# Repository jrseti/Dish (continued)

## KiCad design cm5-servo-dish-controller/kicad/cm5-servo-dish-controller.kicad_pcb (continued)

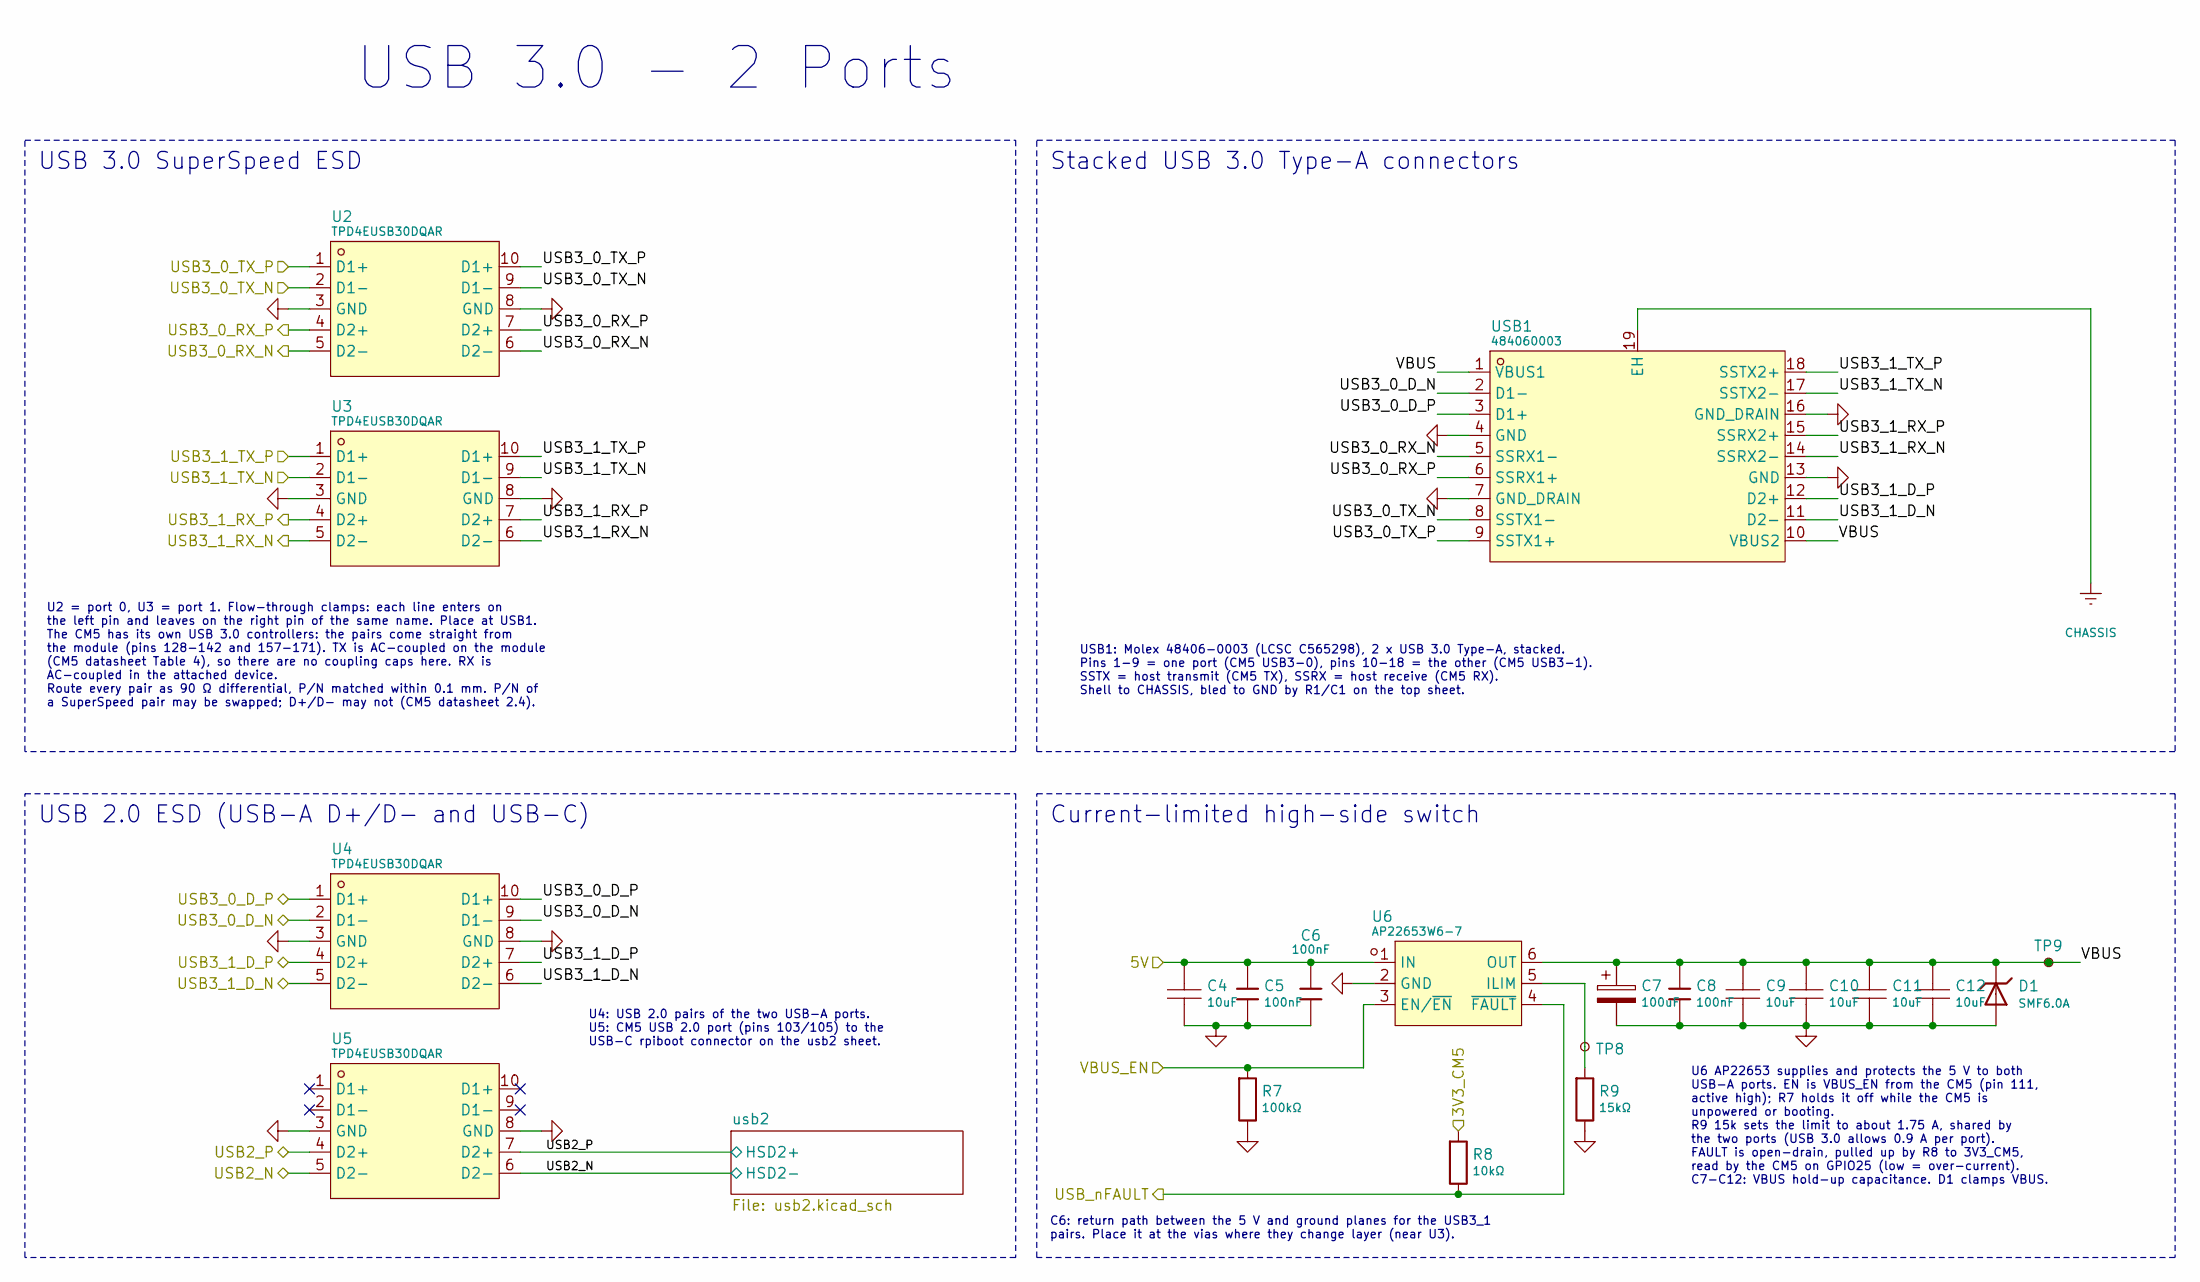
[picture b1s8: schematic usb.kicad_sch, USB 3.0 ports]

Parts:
C4, C9, C10, C11, C12: 10uF; CAPC2012X145N; Tolerance ±10%; Voltage Rating 10V; MPN CL21B106KPQNNNE; LCSC Part C32635
C5, C6, C8: 100nF; CAPC1005X55N; Tolerance ±10%; Voltage Rating 16V; MPN CL05B104KO5NNNC; LCSC Part C1525
C7: 100uF; CAPMP7343X310N; Tolerance ±20%; Voltage Rating 10V; MPN SA11AM101A19R15XXX; LCSC Part C135491
D1: SMF6.0A; SODFL3718X110N; MPN SMF6.0A; LCSC Part C19077499
R7: 100kΩ; RESC1608X55N; Tolerance ±1%; Voltage Rating 75V; MPN 0603WAF1003T5E; LCSC Part C25803
R8: 10kΩ; RESC1005X40N; Tolerance ±1%; Voltage Rating 50V; MPN 0402WGF1002TCE; LCSC Part C25744
R9: 15kΩ; RESC1005X40N; Tolerance ±1%; Voltage Rating 50V; MPN 0402WGF1502TCE; LCSC Part C25756
TP8, TP9: TestPoint_Small; TestPoint_Pad_D0.8mm
U2, U3, U4, U5: TPD4EUSB30DQAR; SON50P100X250X60-10N; MPN TPD4EUSB30DQAR; LCSC Part C90627
U6: AP22653W6-7; SOT95P280X145-6N; MPN AP22653W6-7; LCSC Part C2158037
USB1: 484060003; Molex_48406-0003; MPN 484060003; LCSC Part C565298

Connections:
/3V3_CM5: R8.1; also elsewhere on the board
/5V: C4.1, C5.1, C6.1, U6.1 (IN); also elsewhere on the board
/CM5/USB2_N: U5.5 (D2-), U5.6 (D2-); also elsewhere on the board
/CM5/USB2_P: U5.4 (D2+), U5.7 (D2+); also elsewhere on the board
/CM5/USB3_0_D_N: U4.2 (D1-), U4.9 (D1-), USB1.2 (D1-); also elsewhere on the board
/CM5/USB3_0_D_P: U4.1 (D1+), U4.10 (D1+), USB1.3 (D1+); also elsewhere on the board
/CM5/USB3_0_RX_N: U2.5 (D2-), U2.6 (D2-), USB1.5 (SSRX1-); also elsewhere on the board
/CM5/USB3_0_RX_P: U2.4 (D2+), U2.7 (D2+), USB1.6 (SSRX1+); also elsewhere on the board
/CM5/USB3_0_TX_N: U2.2 (D1-), U2.9 (D1-), USB1.8 (SSTX1-); also elsewhere on the board
/CM5/USB3_0_TX_P: U2.1 (D1+), U2.10 (D1+), USB1.9 (SSTX1+); also elsewhere on the board
/CM5/USB3_1_D_N: U4.5 (D2-), U4.6 (D2-), USB1.11 (D2-); also elsewhere on the board
/CM5/USB3_1_D_P: U4.4 (D2+), U4.7 (D2+), USB1.12 (D2+); also elsewhere on the board
/CM5/USB3_1_RX_N: U3.5 (D2-), U3.6 (D2-), USB1.14 (SSRX2-); also elsewhere on the board
/CM5/USB3_1_RX_P: U3.4 (D2+), U3.7 (D2+), USB1.15 (SSRX2+); also elsewhere on the board
/CM5/USB3_1_TX_N: U3.2 (D1-), U3.9 (D1-), USB1.17 (SSTX2-); also elsewhere on the board
/CM5/USB3_1_TX_P: U3.1 (D1+), U3.10 (D1+), USB1.18 (SSTX2+); also elsewhere on the board
/CM5/USB_nFAULT: R8.2, U6.4 (~FAULT); also elsewhere on the board
/CM5/VBUS_EN: R7.1, U6.3 (EN/~EN); also elsewhere on the board
/CM5/usb/VBUS: C7.1, C8.1, C9.1, C10.1, C11.1, C12.1, D1.1, TP9.1 (1_1), U6.6 (OUT), USB1.1 (VBUS1), USB1.10 (VBUS2)
CHASSIS: USB1.19 (EH); also elsewhere on the board
GND: C4.2, C5.2, C6.2, C7.2, C8.2, C9.2, C10.2, C11.2, C12.2, D1.2, R7.2, R9.2, U2.3 (GND), U2.8 (GND), U3.3 (GND), U3.8 (GND), U4.3 (GND), U4.8 (GND), U5.3 (GND), U5.8 (GND), U6.2 (GND), USB1.4 (GND), USB1.7 (GND_DRAIN), USB1.13 (GND), USB1.16 (GND_DRAIN); also elsewhere on the board
unnamed: R9.1, TP8.1 (1_1), U6.5 (ILIM)

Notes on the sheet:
USB 3.0 - 2 Ports
U2 = port 0, U3 = port 1. Flow-through clamps: each line enters on the left pin and leaves on the right pin of the same name. Place at USB1. The CM5 has its own USB 3.0 controllers: the pairs come straight from the module (pins 128-142 and 157-171). TX is AC-coupled on the module (CM5 datasheet Tab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
USB 2.0 ESD (USB-A D+/D- and USB-C)
Stacked USB 3.0 Type-A connectors
U6 AP22653 supplies and protects the 5 V to both USB-A ports. EN is VBUS_EN from the CM5 (pin 111, active high); R7 holds it off while the CM5 is unpowered or booting. R9 15k sets the limit to about 1.75 A, shared by the two ports (USB 3.0 allows 0.9 A per port). FAULT is open-drain, pulled up by R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
C6: return path between the 5 V and ground planes for the USB3_1 pairs. Place it at the vias where they change layer (near U3).
USB 3.0 SuperSpeed ESD
USB1: Molex 48406-0003 (LCSC C565298), 2 x USB 3.0 Type-A, stacked. Pins 1-9 = one port (CM5 USB3-0), pins 10-18 = the other (CM5 USB3-1). SSTX = host transmit (CM5 TX), SSRX = host receive (CM5 RX). Shell to CHASSIS, bled to GND by R1/C1 on the top sheet.
U4: USB 2.0 pairs of the two USB-A ports. U5: CM5 USB 2.0 port (pins 103/105) to the USB-C rpiboot connector on the usb2 sheet.
Current-limited high-side switch

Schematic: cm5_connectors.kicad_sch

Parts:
C14: 100nF; CAPC1005X55N; Tolerance ±10%; Voltage Rating 16V; MPN CL05B104KO5NNNC; LCSC Part C1525
F1: 100mA; FUSC1608X100N; MPN SMD0603-010-24V; LCSC Part C70048
H6: Header-Male-2.54_1x2; PinHeader_1x02_P2.54mm_Vertical; MPN B-2100S02P-A110; LCSC Part C124375
J3: 2541WV-2X12P; PinHeader_2x12_P2.54mm_Vertical; MPN 2541WV-2x12P; LCSC Part C5383110
J4: Header-Male-2.54_1x3; PinHeader_1x03_P2.54mm_Vertical; MPN 2.54-1*3PPin; LCSC Part C49257
J5: Header-Male-2.54_2x3; PinHeader_2x03_P2.54mm_Vertical; MPN 2.54-2*3PPin; LCSC Part C65114
R12, R13: 2.2kΩ; RESC1005X40N; Tolerance ±1%; Voltage Rating 50V; MPN 0402WGF2201TCE; LCSC Part C25879
U9: 74LVC1G07SE-7; SOT65P210X110-5N; MPN 74LVC1G07SE-7; LCSC Part C67531

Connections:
/3V3_CM5: C14.1, F1.1, H6.1, U9.5 (VCC); also elsewhere on the board
/5V: J3.7; also elsewhere on the board
/CM5/BOOT_CONSOLE_RXD: J4.1; also elsewhere on the board
/CM5/BOOT_CONSOLE_TXD: J4.2; also elsewhere on the board
/CM5/CM5_Connectors/I2C1_PU: H6.2, R12.1, R13.1
/CM5/EEPROM_nWP: J5.4; also elsewhere on the board
/CM5/GPIO0: J3.13; also elsewhere on the board
/CM5/GPIO17: J3.20; also elsewhere on the board
/CM5/GPIO19: J3.11; also elsewhere on the board
/CM5/GPIO22: J3.21; also elsewhere on the board
/CM5/GPIO26: J3.9; also elsewhere on the board
/CM5/GPIO27: J3.23; also elsewhere on the board
/CM5/I2C1_SCL: J3.22, R13.2; also elsewhere on the board
/CM5/I2C1_SDA: J3.24, R12.2; also elsewhere on the board
/CM5/PMIC_EN: J5.6; also elsewhere on the board
/CM5/SPI0_CE0: J3.14; also elsewhere on the board
/CM5/SPI0_CE1: J3.12; also elsewhere on the board
/CM5/SPI0_MISO: J3.17; also elsewhere on the board
/CM5/SPI0_MOSI: J3.19; also elsewhere on the board
/CM5/SPI0_SCLK: J3.15; also elsewhere on the board
/CM5/nPWR_CYCLE: U9.2 (A); also elsewhere on the board
/CM5/nRPIBOOT: J5.2; also elsewhere on the board
GND: C14.2, J3.1, J3.2, J3.3, J3.4, J3.6, J3.8, J3.10, J3.16, J3.18, J4.3, J5.1, J5.3, U9.3 (GND); also elsewhere on the board
unnamed: F1.2, J3.5
unnamed: J5.5, U9.4 (Y)

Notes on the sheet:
Boot Console UART
I2C Pull-Ups
GPIO2
GPIO0 (J3-13) as plain GPIO: add to config.txt force_eeprom_read=0 disable_poe_fan=1 or the firmware probes GPIO0/1 (I2C0) for a HAT EEPROM at boot.
EEPROM WRITE PROTECT (EEPROM_nWP, J5 3-4) The CM5 pulls EEPROM_nWP up internally (100k), so the bootloader EEPROM is writable unless J5 3-4 is fitted. The jumper only takes effect once protection is enabled in the bootloader config (CM5 datasheet 2.12.2). Production: - Set eeprom_write_protect=1 in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
H6: optional I2C1 pull-ups R12/R13, normally OPEN. CM5 already pulls GPIO2/3 up with 1.8k (CM5 datasheet Table 4). Fit H6 only for a long, high-capacitance bus at 400 kHz: ~1k total, ~2.9 mA sink at 0.4 V (I2C spec min 3 mA, so compliant devices are OK).
I2C PULL-UPS I2C1: GPIO2 = I2C1_SDA (J3-24), GPIO3 = I2C1_SCL (J3-22) Pulled up to 3.3 V (GPIO_VREF) by 1.8 kΩ inside the CM5 (CM5 datasheet Table 4, pins 56/58). No board pull-ups are needed. R12/R13 (2.2k, fitted via H6) are optional.
EEPROM write protect = Jumper Pins 3-4
GPIO3
CONSOLE UART (J4): CM5 UART0, 3.3 V logic, 115200 baud, 8N1, no flow control J4-1 BOOT_CONSOLE_RXD (GPIO15, CM5 receives) <- adapter TXD J4-2 BOOT_CONSOLE_TXD (GPIO14, CM5 transmits) -> adapter RXD J4-3 GND -- adapter GND TX and RX cross over: the adapter TXD goes to the CM5 RXD. Use an inexpensive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
J3 pins 2 and 4 are GND. On the CM4 board they were the AIN0/AIN1 ADC inputs. The CM5 has no ADC pins (module pins 94/96 are now CC1/CC2), so the inputs and their clamps are removed.
CM5 External Header Pins
GPIO9
GPIO10
Boot/EEPROM_EN/PMIC_EN
POWER-CYCLE CONTROL (nPWR_CYCLE) Lets the CM5 cut its own power after a clean shutdown and restart by itself. Use it when a normal reboot is not enough: it fully resets the PMIC and all on-module power rails. How it works: - GPIO6 drives U9 (74LVC1G07, open-drain). J5 pins 5-6 connect U9's output t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
GPIO8
GPIO7
Force RPIBOOT = Jumper Pins 1-2
F1 (100 mA PTC, SMD0603-010-24V) fuses the 3.3 V on J3 pin 5: a short on a plug-in board trips F1, not the CM5 rail. HAT budget 100 mA; CN1 has F3.
GPIO Headers
GPIO11

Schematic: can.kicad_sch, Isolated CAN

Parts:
C46, C47, C50, C51, C52, C62: 100nF; CAPC1005X55N; Tolerance ±10%; Voltage Rating 16V; MPN CL05B104KO5NNNC; LCSC Part C1525
C48, C53: 1uF; CAPC1608X95N; Tolerance ±10%; Voltage Rating 50V; MPN CL10A105KB8NNNC; LCSC Part C15849
C49, C57, C60: 2.2uF; CAPC3216X180N; MPN CL31Y225KCHVPNE; LCSC Part C2803390
C54: 2.2nF; CAPRD1000W55L820T450; Tolerance ±20%; Voltage Rating 400VAC Y1; MPN AJTF222M2GF0200A082E; LCSC Part C2836435; not fitted
C55: 220nF; CAPC1005X55N; Tolerance ±10%; Voltage Rating 25V; MPN TCC0402X7R224K250AT; LCSC Part C915854
C56: 100uF; CAPAE1030X1250N; MPN EFVH100ADA101M10C0; LCSC Part C22387799
C58, C64: 4.7nF; CAPC3216X180N; Tolerance ±10%; Voltage Rating 2kV; MPN 1206B472K202NT; LCSC Part C41017; not fitted
C59: 4.7nF; CAPC2012X145N; Tolerance ±5%; Voltage Rating 50V; MPN GRM2165C1H472JA01D; LCSC Part C77063
C61: 100nF; CAPC1608X95N; Tolerance ±10%; Voltage Rating 100V; MPN CL10B104KC8NNNC; LCSC Part C15725
C63: 22uF; CAPC2012X145N; Tolerance ±20%; Voltage Rating 25V; MPN CL21A226MAYNNNE; LCSC Part C602037
D8: SMBJ28CA; DIOM5436X244N; MPN SMBJ28CA; LCSC Part C151259
D9, D11: PESD2CANFD27V; SOT95P240X110-3N; MPN PESD2CANFD27V-TR-(TP); LCSC Part C54561881
D10: SS210; DIOM5226X244N; MPN SS210; LCSC Part C14996
D12: SMBJ28A; DIOM5436X244N; MPN SMBJ28A; LCSC Part C178227
J11: KF2EDGR-5.08-2P; KEFA_KF2EDGR-5.08-2P; MPN KF2EDGR-5.08-2P; LCSC Part C441204
J12, J13: RJ45; Kinghelm_KH-RJ45-58-8P8C; MPN KH-RJ45-58-8P8C; LCSC Part C2683360
L2: 51uH; TDK_ACT45B; MPN ACT45B-510-2P-TL003; LCSC Part C76584
L3: 33uH; INDM6060X450N; Tolerance ±20%; Current Rating 1.5A; MPN SMNR6045-330MT; LCSC Part C135306
LED7: GREEN; LEDC2012X110N; MPN KT-0805G; LCSC Part C2297
R38: 33Ω; RESC1005X40N; Tolerance ±1%; Voltage Rating 50V; MPN 0402WGF330JTCE; LCSC Part C25105
R39, R42, R47: 10kΩ; RESC1005X40N; Tolerance ±1%; Voltage Rating 50V; MPN 0402WGF1002TCE; LCSC Part C25744
R40: 249kΩ; RESC1608X55N; Tolerance ±1%; Voltage Rating 75V; MPN 0603WAF2493T5E; LCSC Part C22918
R41: 30kΩ; RESC1005X40N; Tolerance ±1%; Voltage Rating 50V; MPN 0402WGF3002TCE; LCSC Part C25776
R43: 24kΩ; RESC1005X40N; Tolerance ±1%; Voltage Rating 50V; MPN 0402WGF2402TCE; LCSC Part C25769
R44, R45: 0Ω; RESC1608X55N; Tolerance ±1%; Voltage Rating 75V; MPN 0603WAF0000T5E; LCSC Part C21189; not fitted
R46: 20kΩ; RESC1005X40N; Tolerance ±1%; Voltage Rating 50V; MPN 0402WGF2002TCE; LCSC Part C25765
R48, R50: 47kΩ; RESC1005X40N; Tolerance ±1%; Voltage Rating 50V; MPN 0402WGF4702TCE; LCSC Part C25792
R49, R60: 0Ω; RESC3216X70N; Tolerance ±1%; Voltage Rating 200V; MPN 1206W4F0000T5E; LCSC Part C17888
R51, R59: 1MΩ; RESC3216X70N; Tolerance ±1%; Voltage Rating 200V; MPN 1206W4F1004T5E; LCSC Part C17927; not fitted
R52: 0Ω; RESC1608X55N; Tolerance ±1%; Voltage Rating 75V; MPN 0603WAF0000T5E; LCSC Part C21189
R53: 10kΩ; RESC1608X55N; Tolerance ±1%; Voltage Rating 75V; MPN 0603WAF1002T5E; LCSC Part C25804
R54, R55: 60.4Ω; RESC3216X70N; Tolerance ±1%; Voltage Rating 200V; MPN 1206W4F604JT5E; LCSC Part C57572
R56: 100kΩ; RESC1608X55N; Tolerance ±1%; Voltage Rating 75V; MPN 0603WAF1003T5E; LCSC Part C25803
R57: 118kΩ; RESC1005X40N; Tolerance ±1%; Voltage Rating 50V; MPN 0402WGF1183TCE; LCSC Part C25748
R58: 22.1kΩ; RESC1005X40N; Tolerance ±1%; Voltage Rating 50V; MPN FRC0402F2212TS; LCSC Part C2929993
SW2: 2xSPST; SOP127P835X250-4N; MPN DSHP02TSGER; LCSC Part C3293142
TP31, TP32, TP33, TP34, TP35, TP36, TP37, TP38, TP39, TP40, TP41: TestPoint_Small; TestPoint_Pad_D0.8mm
U17: ISO1042DWR; SOIC127P1030X265-16N; MPN ISO1042DWR; LCSC Part C1848126
U18: ISO7721DWR; SOIC127P1030X265-16N; MPN ISO7721DWR; LCSC Part C524805
U19: TPS26600PWPR; SOP65P640X120-17N; MPN TPS26600PWPR; LCSC Part C544399
U20: LMR51606XDBVR; SOT95P280X145-6N; MPN LMR51606XDBVR; LCSC Part C21260865

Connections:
/STM32/3V3_MCU: C46.1, C47.1, C48.1, R39.1, U17.1 (VCC1), U18.3 (VCC1); also elsewhere on the board
/STM32/CAN/5V_ISO: C50.1, C51.1, C52.1, C53.1, C63.1, L3.2, R48.1, R57.1, TP41.1 (1_1), U17.11 (VCC2), U17.16 (VCC2), U18.14 (VCC2)
/STM32/CAN/24V_ISO_IN: C49.1, D8.2, D10.2 (A), J11.1, R40.1, U19.1 (IN), U19.2 (IN)
/STM32/CAN/BUCK_FB: R57.2, R58.1, TP40.1 (1_1), U20.3 (FB)
/STM32/CAN/CANH_T: L2.1, R44.1, U17.13 (CANH)
/STM32/CAN/CANL_T: L2.2, R45.1, U17.12 (CANL)
/STM32/CAN/CAN_H: D9.2, D11.2, J12.1, J13.1, L2.4, R44.2, SW2.4, TP36.1 (1_1)
/STM32/CAN/CAN_L: D9.1, D11.1, J12.2, J13.2, L2.3, R45.2, SW2.3, TP37.1 (1_1)
/STM32/CAN/CAN_V+: C56.1, C57.1, D12.1 (C), J13.8, R53.1, TP35.1 (1_1), U19.15 (OUT), U19.16 (OUT)
/STM32/CAN/EFUSE_RTN: C55.2, R42.2, R43.2, U19.6 (MODE), U19.8 (RTN), U19.17 (EP)
/STM32/CAN/EN_ISO: R47.2, U18.12 (OUTB)
/STM32/CAN/FLT_ISO: R50.2, U18.13 (INA)
/STM32/CAN/SHLD_A: C58.1, J12.9, J12.10, R49.1, R51.1
/STM32/CAN/SHLD_B: C64.1, J13.9, J13.10, R59.1, R60.1
/STM32/CAN/VIN_BUCK: C60.1, C61.1, D10.1 (K), R56.1, TP38.1 (1_1), U20.5 (VIN)
/STM32/CAN_RX: U17.5 (RXD); also elsewhere on the board
/STM32/CAN_TX: R38.1; also elsewhere on the board
/STM32/CAN_VBUS_EN: U18.5 (INB); also elsewhere on the board
/STM32/CAN_VBUS_FLT: U18.4 (OUTA); also elsewhere on the board
CHASSIS: C58.2, C64.2, R49.2, R51.2, R59.2, R60.2; also elsewhere on the board
GND: C46.2, C47.2, C48.2, C54.1, U17.2 (GND1), U17.8 (GND1), U18.1 (GND1), U18.7 (GND1); also elsewhere on the board
GND_ISO: C49.2, C50.2, C51.2, C52.2, C53.2, C54.2, C56.2, C57.2, C59.2, C60.2, C61.2, C63.2, D8.1, D9.3, D11.3, D12.2 (A), J11.2, J13.3, J13.7, LED7.2 (K), R46.2, R52.2, R58.2, TP31.1 (1_1), U17.9 (GND2), U17.10 (GND2), U17.15 (GND2), U18.9 (GND2), U18.16 (GND2), U19.9 (GND), U20.2 (GND)
unnamed: C59.1, R54.2, R55.2
unnamed: J12.3, R52.1
unnamed: LED7.1 (A), R53.2, TP34.1 (1_1)
unnamed: R54.1, SW2.1
unnamed: R55.1, SW2.2
unnamed: R38.2, R39.2, U17.3 (TXD)
unnamed: R43.1, TP33.1 (1_1), U19.11 (ILIM)
unnamed: R41.2, R42.1, U19.5 (OVP)
unnamed: R40.2, R41.1, TP32.1 (1_1), U19.3 (UVLO)
unnamed: C55.1, U19.12 (dVdT)
unnamed: R48.2, R50.1, U19.14 (~FLT)
unnamed: R46.1, R47.1, U19.7 (~SHDN)
unnamed: C62.1, U20.1 (CB)
unnamed: R56.2, TP39.1 (1_1), U20.4 (EN)
unnamed: C62.2, L3.1, U20.6 (SW)

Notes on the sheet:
Digital isolator for the eFuse enable and fault signals
Isolated CAN transceiver and common-mode choke
Isolated CAN section, 2-jack single-bus version (design brief plans/isolated-can-section-brief.md, rev C1). This board is the CANopen master in the middle of one linear bus: [120 ohm] drive EL -- drive AZ -- J12 == this board == J13 -- weather bridge -- AZ node -- EL node [120 ohm] Three domains, k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
Isolated CAN (CANopen)
J12 CAN A - drives (no power)
GND_ISO
5V_ISO supply for the isolated side
U18 ISO7721 (DW, SOIC-16 wide, 8 mm creepage) crosses the same isolation barrier as U17. CAN_VBUS_EN (PC8): high or not driven = dish-side CAN_V+ on, low = off. The ISO7721 output defaults high when its input is open or the logic side is unpowered, so CAN_V+ comes up without firmware. CAN_VBUS_FLT 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
+24 V GND_ISO
CAN bus through-path, protection, termination and RJ45 jacks
J12 = CAN A, drive side (to DSY-C CN1). J13 = CAN B, dish side (weather bridge, AZ node, EL node). Silkscreen J13 "CAN + 24 V OUT - DISH": it carries power that must never reach a drive. Both jacks use the CiA 303-1 pinout: pin 1 CAN_H, pin 2 CAN_L. CAN_H / CAN_L run straight from J12 to J13 as one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
stub to L2 / U17
SW2 default OFF
J13 CAN B - dish (CAN_V+ out)
J11: 24 V from the external isolated Mean Well 48 V to 24 V converter. Its -V output stays floating: no bond to PE or to board GND. D8 SMBJ28CA (28 V stand-off, 45 V clamp) is bidirectional, so a reversed supply is blocked by U19 and not shorted by the TVS. U19 TPS26600 eFuse: current limit 12 / R4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
U17 ISO1042 (DW, SOIC-16 wide): isolated CAN FD transceiver, 5 Mbit/s, 5 kVrms, +/-70 V bus fault protection. Logic side on 3V3_MCU / GND: C46 100 nF + C48 1 uF at VCC1. Bus side on 5V_ISO / GND_ISO: this package has two VCC2 pins, each with its own 100 nF (C50 at pin 16, C52 at pin 11), plus C53 1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
24 V isolated input and CAN_V+ eFuse (dish-side bus power)
U20 LMR51606X: 65 V, 0.6 A synchronous buck, 400 kHz. Output 0.8 V x (1 + R57 / R58) = 5.07 V. Load: U17 up to about 75 mA while it drives the bus dominant, U18 about 2 mA. D10 feeds it from the input side of the eFuse: U17 keeps talking to the drives while CAN_V+ is switched off. D10 also blocks a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

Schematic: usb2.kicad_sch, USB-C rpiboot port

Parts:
D7: SMF6.0A; SODFL3718X110N; MPN SMF6.0A; LCSC Part C19077499
R36, R37: 5.1kΩ; RESC1005X40N; Tolerance ±1%; Voltage Rating 50V; MPN 0402WGF5101TCE; LCSC Part C25905
TP30: TestPoint_Small; TestPoint_Pad_D0.8mm
USBC1: TYPE-C-31-M-12; HRO_TYPE-C-31-M-12; MPN TYPE-C-31-M-12; LCSC Part C165948

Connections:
/CM5/USB2_N: USBC1.A7 (DN1), USBC1.B7 (DN2); also elsewhere on the board
/CM5/USB2_P: USBC1.A6 (DP1), USBC1.B6 (DP2); also elsewhere on the board
/CM5/usb/usb2/VBUS_USBC: D7.1, TP30.1 (1_1), USBC1.A4B9 (VBUS), USBC1.B4A9 (VBUS)
CHASSIS: USBC1.1 (EH), USBC1.2 (EH), USBC1.3 (EH), USBC1.4 (EH); also elsewhere on the board
GND: D7.2, R36.2, R37.2, USBC1.A1B12 (GND), USBC1.B1A12 (GND); also elsewhere on the board
unnamed: R36.1, USBC1.A5 (CC1)
unnamed: R37.1, USBC1.B5 (CC2)

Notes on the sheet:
USB-C Port for CM5 Flashing (rpiboot)
USB-C carries the CM5 USB 2.0 port (module pins 103/105). It is a device port for rpiboot (eMMC flashing) only. There is no mux: on the CM5 the two USB-A ports have their own USB 3.0 controllers. USB_OTG_ID (module pin 101) is left open = device role. USBC1 VBUS is not used (the board takes no powe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

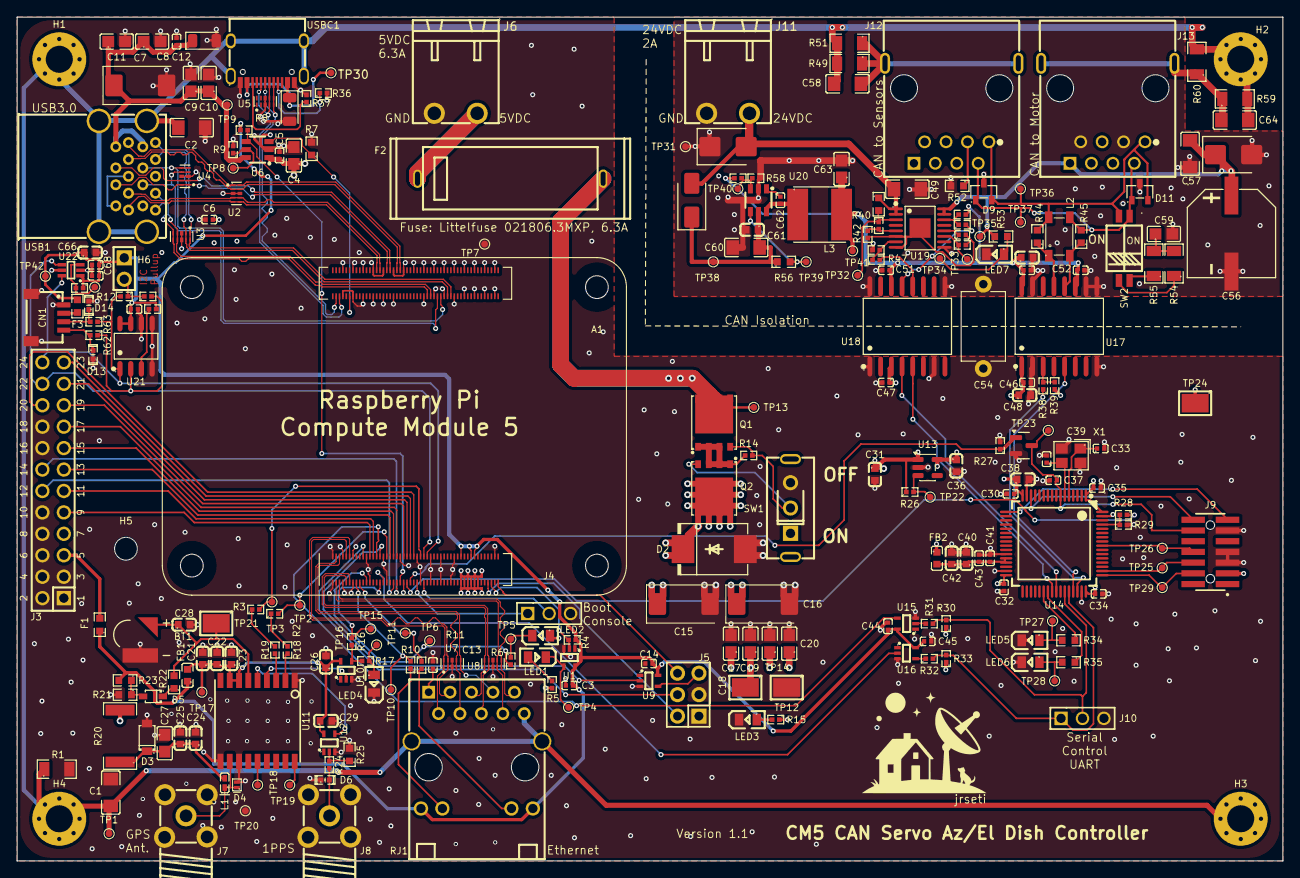
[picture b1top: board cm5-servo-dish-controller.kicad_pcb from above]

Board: 4 copper layers, 150.0 x 100.0 mm, 259 parts (1 on the bottom side), 154 nets.

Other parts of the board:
LOGO1: LOGO; house-dog-logo
LOGO2: dog-ufo-logo

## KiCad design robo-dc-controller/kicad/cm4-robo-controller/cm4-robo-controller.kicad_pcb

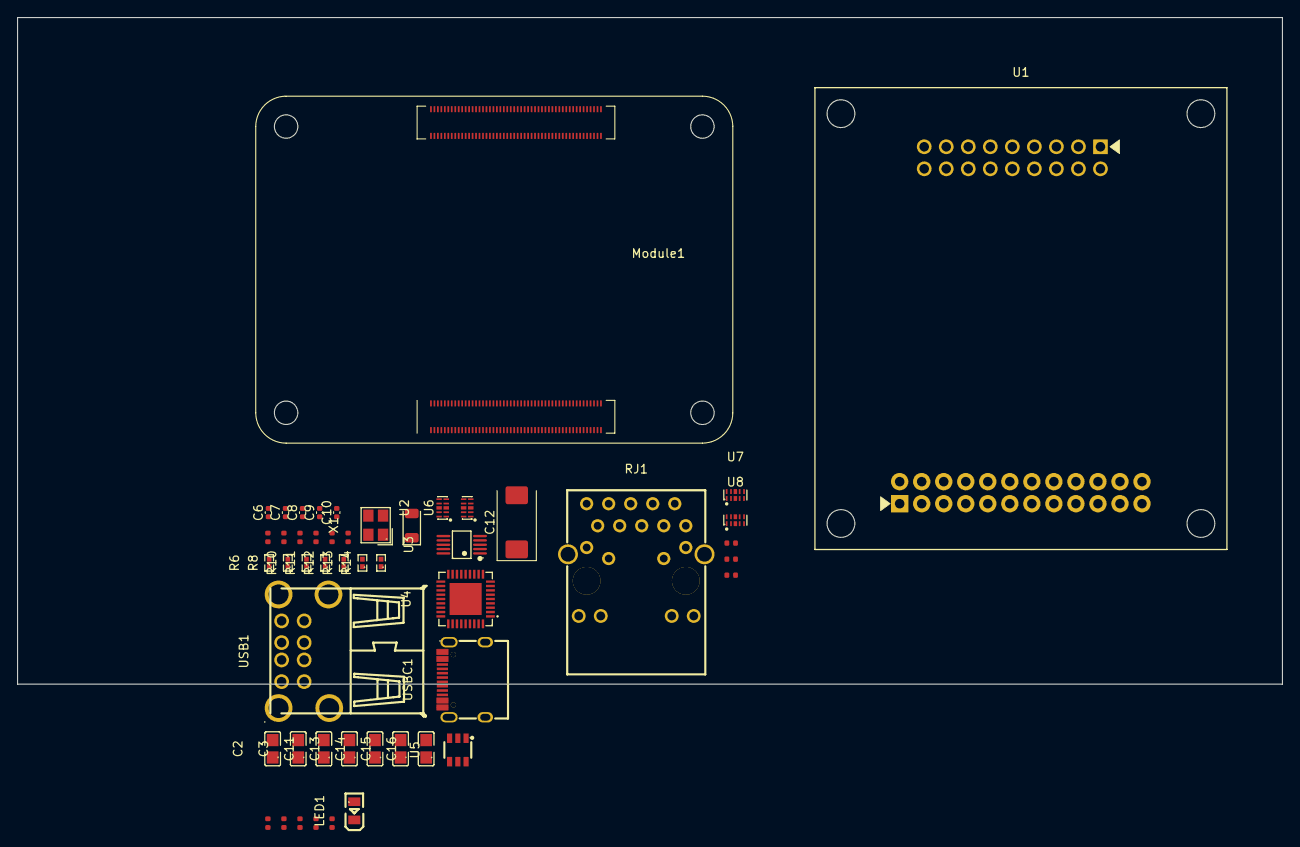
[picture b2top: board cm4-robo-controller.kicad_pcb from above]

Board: 2 copper layers, 145.8 x 76.9 mm, 49 parts (0 on the bottom side), 48 nets, no tracks yet.

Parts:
C1, C4: 15pF; C_0402
C2, C3, C11, C13, C14, C15, C16: 10uF 10V; C0805
C5, C17: 100nF; C_0402
C6, C7, C8, C9, C10: 100n; C_0402_1005Metric
C12: 100uF 6.3V; CP_EIA-7343-31_Kemet-D
D1: SMF6.0A; D_SOD-123FL
LED1: RED; LED0805-R-RD
Module1: ComputeModule4-CM4; Raspberry-Pi-4-Compute-Module
R1: 10kΩ; R_0402
R2, R3, R4: 100Ω; R_0402
R5, R16, R17: 1.5kΩ; R_0402
R6, R8: 2.2kΩ; R0402
R7, R9: 5.1kΩ; R_0402
R10, R11, R13, R14: 36K 1%; R0402
R12: 12kΩ; R0402
R15: 15kΩ; R_0402
RJ1: LPJG0926HENL_C22457393; RJ45-TH_LPJG0926HENL_C22457393
U1: ROBOCLAW-2X15A-OEM; MOD-TH_ROBOCLAW-OEM-2X15A
U2, U6: TPD4EUSB30DQAR-N; DFN-10_L2.5-W1.0-P0.50-BL-A
U3: FSUSB42MUX; MSOP-10_L3.0-W3.0-P0.50-LS5.0-BL
U4: USB2514B-I/M2; SQFN-36_L6.0-W6.0-P0.50-BL-EP
U5: AP22653W6-7; SOT-23-6_L2.9-W1.6-P0.95-LS2.8-BR
U7, U8: TPD4EUSB30DQAR; USON-10_L2.5-W1.0-P0.50-BL
USB1: Double layer DIP 90° black; USB-A-TH_USB-M-51
USBC1: TYPE-C-31-M-12; USB-C_SMD-TYPE-C-31-M-12_1
X1: X322524MOB4SI; CRYSTAL-SMD_4P-L3.2-W2.5-BL

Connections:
3V3_CM4: C2.2, C3.2, C5.1, C6.1, C7.1, C8.1, C9.1, C10.1, Module1.78 (GPIO_VREF(1.8v/3.3v_Input)), Module1.84 (+3.3v_(Output)), Module1.86 (+3.3v_(Output)), R1.1, U3.1 (VCC), U4.5 (VDDA33), U4.10 (VDDA33), U4.15 (VDD33), U4.23 (VDD33), U4.27 (VBUS_DET), U4.29 (VDDA33), U4.36 (VDDA33)
5V: C11.2, LED1.1 (A), Module1.77 (+5v_(Input)), Module1.79 (+5v_(Input)), Module1.81 (+5v_(Input)), Module1.83 (+5v_(Input)), Module1.85 (+5v_(Input)), Module1.87 (+5v_(Input)), RJ1.15, RJ1.17, U5.1 (IN)
/CM4/EP0+: Module1.12 (Ethernet_Pair0_P), RJ1.1 (TD1+), U7.1 (D1+)
/CM4/EP0-: Module1.10 (Ethernet_Pair0_N), RJ1.2 (TD1-), U7.2 (D1-)
/CM4/EP1+: Module1.4 (Ethernet_Pair1_P), RJ1.3 (TD2+), U7.4 (D2+)
/CM4/EP1-: Module1.6 (Ethernet_Pair1_N), RJ1.6 (TD2-), U7.5 (D2-)
/CM4/EP2+: Module1.11 (Ethernet_Pair2_P), RJ1.7 (TD3+), U8.1 (D1+)
/CM4/EP2-: Module1.9 (Ethernet_Pair2_N), RJ1.8 (TD3-), U8.2 (D1-)
/CM4/EP3+: Module1.3 (Ethernet_Pair3_P), RJ1.9 (TD4+), U8.4 (D2+)
/CM4/EP3-: Module1.5 (Ethernet_Pair3_N), RJ1.10 (TD4-), U8.5 (D2-)
/CM4/ETH_LEDG: Module1.17 (Ethernet_nLED2(3.3v)), R16.1
/CM4/ETH_LEDY: Module1.15 (Ethernet_nLED3(3.3v)), R17.2
/CM4/MCU_nIRQ: R1.2, R2.1
/CM4/USB2_N: Module1.103 (USB2_N), U3.4 (D-)
/CM4/USB2_P: Module1.105 (USB2_P), U3.3 (D+)
/CM4/USB_OTG_ID: Module1.101 (USB_OTG_ID), R6.1, R8.1, U3.2 (Sel)
/CM4/nEXTRST: Module1.100 (nEXTRST), U4.26 (RESET_N)
/CM4/usb/HD1_N: U4.1 (USBDM_DN1/PRT_DIS_M1), U6.5, USB1.6 (D-)
/CM4/usb/HD1_P: U4.2 (USBDP_DN1/PRT_DIS_P1), U6.4, USB1.7 (D+)
/CM4/usb/HD2_N: U4.3 (USBDM_DN2/PRT_DIS_M2), U6.2, USB1.2 (D-)
/CM4/usb/HD2_P: U4.4 (USBDP_DN2/PRT_DIS_P2), U6.1, USB1.3 (D+)
/CM4/usb/HSD2+: U2.1, U3.9 (HSD2+), USBC1.A6 (DP1), USBC1.B6 (DP2)
/CM4/usb/HSD2-: U2.2, U3.8 (HSD2-), USBC1.A7 (DN1), USBC1.B7 (DN2)
/CM4/usb/PWR1: U4.12 (PRTPWR1/BC_EN1), U5.3 (EN/~EN)
/CM4/usb/VBUS: C12.1, C13.2, C14.2, C15.2, C16.2, D1.1, U5.6 (OUT), USB1.1 (VCC), USB1.5 (VCC)
/CM4/usb/nOCS1: U4.13 (OCS_N1), U4.17 (OCS_N2), U4.19 (OCS_N3), U4.21 (OCS_N4), U5.4 (~FAULT)
GND: C1.2, C2.1, C3.1, C4.2, C5.2, C6.2, C7.2, C8.2, C9.2, C10.2, C11.1, C12.2, C13.1, C14.1, C15.1, C16.1, C17.2, D1.2, Module1.1 (GND), Module1.2 (GND), Module1.7 (GND), Module1.8 (GND), Module1.13 (GND), Module1.14 (GND), Module1.22 (GND), Module1.23 (GND), Module1.32 (GND), Module1.33 (GND), Module1.42 (GND), Module1.43 (GND), Module1.52 (GND), Module1.53 (GND), Module1.59 (GND), Module1.60 (GND), Module1.65 (GND), Module1.66 (GND), Module1.71 (GND), Module1.74 (GND), Module1.98 (GND), Module1.107 (GND), Module1.108 (GND), Module1.113 (GND), Module1.114 (GND), Module1.119 (GND), Module1.120 (GND), Module1.125 (GND), Module1.126 (GND), Module1.131 (GND), Module1.132 (GND), Module1.137 (GND), Module1.138 (GND), Module1.144 (GND), Module1.150 (GND), Module1.155 (GND), Module1.156 (GND), Module1.161 (GND), Module1.162 (GND), Module1.167 (GND), Module1.168 (GND), Module1.173 (GND), Module1.174 (GND), Module1.179 (GND), Module1.180 (GND), Module1.185 (GND), Module1.186 (GND), Module1.191 (GND), Module1.192 (GND), Module1.197 (GND), Module1.198 (GND), R6.2, R7.2, R9.2, R10.1, R11.1, R12.1, R13.1, R14.1, R15.2, RJ1.19 (EH), RJ1.20 (EH), U2.3, U2.8, U3.5 (GND), U3.10 (~OE), U4.37 (EP), U5.2 (GND), U6.3, U6.8, U7.3 (GND), U7.8 (GND), U8.3 (GND), U8.8 (GND), USB1.4 (GND), USB1.8 (GND), USB1.9, USBC1.1 (EH), USBC1.2 (EH), USBC1.3 (EH), USBC1.4 (EH), USBC1.A1B12 (GND), USBC1.B1A12 (GND), X1.2 (GND), X1.4 (GND)
unnamed: C17.1, RJ1.4 (CT), RJ1.5 (CT)
unnamed: LED1.2 (K), R5.1
unnamed: Module1.54 (GPIO4), R4.2
unnamed: Module1.34 (GPIO5), R3.2
unnamed: Module1.30 (GPIO6), R2.2
unnamed: Module1.21 (PI_nLED_Activity), R5.2
unnamed: R8.2, USBC1.A4B9 (VBUS), USBC1.B4A9 (VBUS)
unnamed: R16.2, RJ1.16
unnamed: R17.1, RJ1.18
unnamed: U3.7 (HSD1+), U4.31 (USBDP_UP)
unnamed: U3.6 (HSD1-), U4.30 (USBDM_UP)
unnamed: R14.2, U4.25 (HS_IND/CFG_SEL1)
unnamed: R12.2, U4.35 (RBIAS)
unnamed: R10.2, U4.24 (SCL/SMBCLK/CFG_SEL0)
unnamed: R11.2, U4.22 (SDA/SMBBATA/NON_REM1)
unnamed: R13.2, U4.28 (SUSP_IND/LOCAL_PWR/NON_REM0)
unnamed: C1.1, U4.33 (XTALIN/CLKIN), X1.1 (OSC1)
unnamed: C4.1, U4.32 (XTALOUT), X1.3 (OSC2)
unnamed: R15.1, U5.5 (ILIM)
unnamed: R7.1, USBC1.A5 (CC1)
unnamed: R9.1, USBC1.B5 (CC2)
